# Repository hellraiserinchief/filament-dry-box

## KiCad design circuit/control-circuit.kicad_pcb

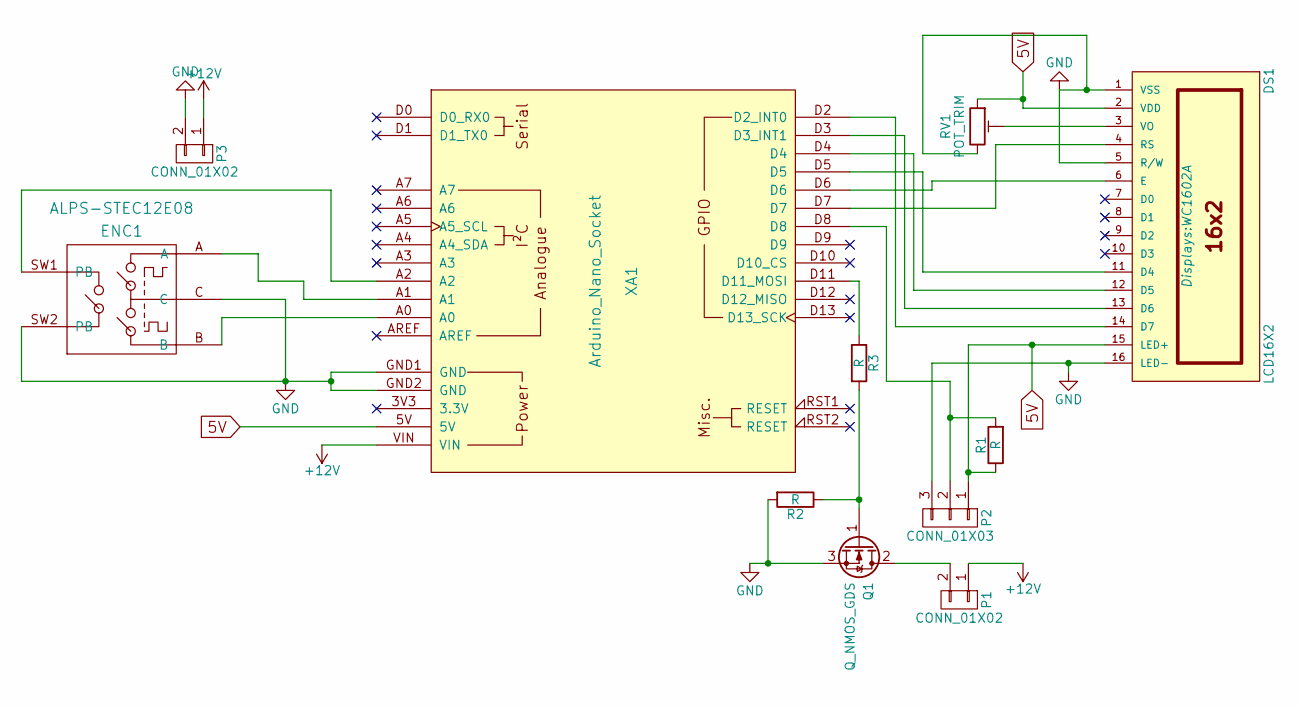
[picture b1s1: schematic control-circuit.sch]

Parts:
DS1: LCD16X2; WC1602A
ENC1: ALPS-STEC12E08; ALPS_STEC12E08
P1, P3: CONN_01X02; TerminalBlock_RND_205-00232_Pitch5.08mm
P2: CONN_01X03; Pin_Header_Straight_1x03
Q1: Q_NMOS_GDS; TO-220_Neutral123_Vertical_LargePads
R1, R2, R3: R; Resistor_Horizontal_RM10mm
RV1: POT_TRIM; Potentiometer_Trimmer-EVM3E
XA1: Arduino_Nano_Socket

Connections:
5V: DS1.2 (VDD), DS1.15 (LED+), P2.1, R1.1, RV1.1, XA1.5V
+12V: P1.1, P3.1, XA1.VIN
GND: DS1.1 (VSS), DS1.5 (R/W), DS1.16 (LED-), ENC1.C, ENC1.SW2 (PB), P2.3, P3.2, Q1.3 (S), R2.2, RV1.3, XA1.GND1 (GND), XA1.GND2 (GND)
unnamed: DS1.3 (VO), RV1.2
unnamed: DS1.4 (RS), XA1.D7
unnamed: DS1.6 (E), XA1.D6
unnamed: DS1.11 (D4), XA1.D5
unnamed: DS1.12 (D5), XA1.D4
unnamed: DS1.13 (D6), XA1.D3 (D3_INT1)
unnamed: DS1.14 (D7), XA1.D2 (D2_INT0)
unnamed: ENC1.A, XA1.A1
unnamed: ENC1.B, XA1.A0
unnamed: ENC1.SW1 (PB), XA1.A2
unnamed: P1.2, Q1.2 (D)
unnamed: P2.2, R1.2, XA1.D8
unnamed: Q1.1 (G), R2.1, R3.2
unnamed: R3.1, XA1.D11 (D11_MOSI)

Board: 2 copper layers, 11 parts (0 on the bottom side), 17 nets, no tracks yet.

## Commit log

2018-07-29 added code for arduino nano
2018-10-07 added 3d models and also added gate restistor
2018-11-03 added pcb case
2018-11-03 fixed pcb case top
2018-11-03 corrected positions od pcb components
2020-02-17 commit old changes
